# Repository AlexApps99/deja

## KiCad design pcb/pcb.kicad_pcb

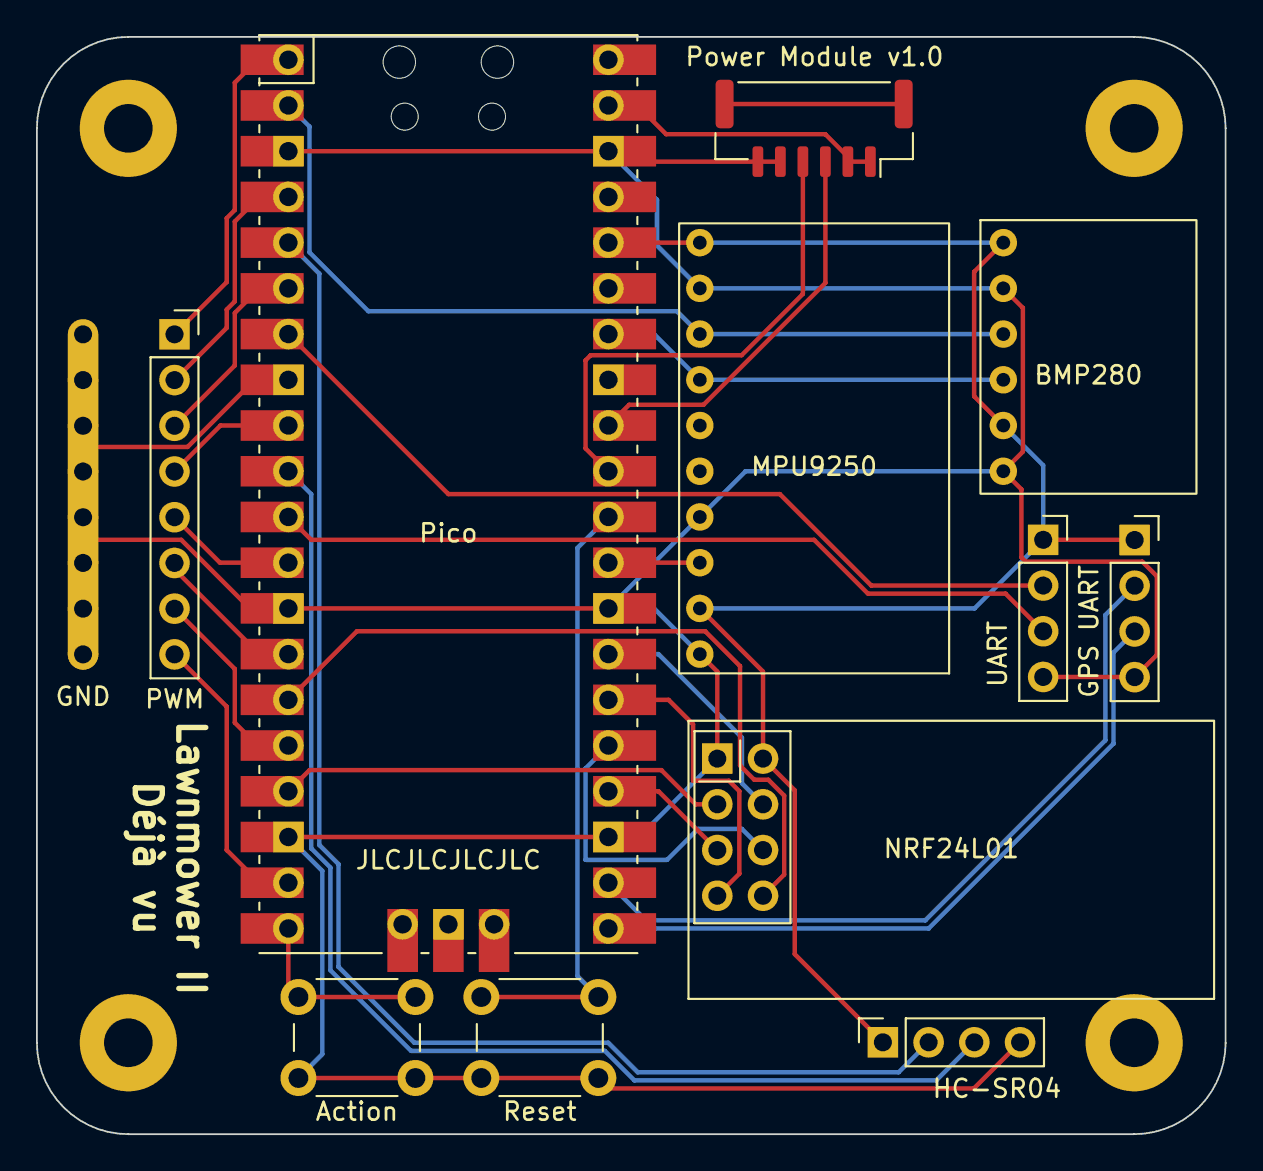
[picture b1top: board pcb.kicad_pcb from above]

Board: 2 copper layers, 66.0 x 61.0 mm, 12 parts (0 on the bottom side), 30 nets.

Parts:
J1: GND; PowerRail8
J2: HC-SR04; PinSocket_1x04_P2.54mm_Vertical
J3: PWM; PinSocket_1x08_P2.54mm_Vertical
J4: GPS UART; PinSocket_1x04_P2.54mm_Vertical
J5: Power Module v1.0; JST_GH_SM06B-GHS-TB_1x06-1MP_P1.25mm_Horizontal
J6: UART; PinSocket_1x04_P2.54mm_Vertical
SW1: Reset; SW_PUSH_6mm_H8mm
SW2: Action; SW_PUSH_6mm_H8mm
U1: Pico; RPi_Pico_SMD_TH
U2: NRF24L01; nRF24L01_Breakout
U3: MPU9250
U4: BMP280

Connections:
+3.3V: J2.1, J4.1, J6.1, U1.36 (3V3), U2.2 (VCC), U3.1 (VCC), U3.9 (NCS), U4.1 (VIN), U4.5 (CSB)
GND: J1.1, J2.4, J4.4, J5.5 (GND), J5.6 (GND), J6.4, SW1.2, SW2.2, U1.3 (GND), U1.8 (GND), U1.13 (GND), U1.18 (GND), U1.23 (GND), U1.28 (GND), U1.38 (GND), U2.1 (GND), U3.2 (GND), U3.7 (AD0), U3.10 (FSYNC), U4.2 (GND), U4.6 (SDD)
unnamed: J2.2, U1.5 (GPIO3)
unnamed: J2.3, U1.10 (GPIO7)
unnamed: J3.1, U1.1 (GPIO0)
unnamed: J3.2, U1.4 (GPIO2)
unnamed: J3.3, U1.6 (GPIO4)
unnamed: J3.4, U1.9 (GPIO6)
unnamed: J3.5, U1.12 (GPIO9)
unnamed: J3.6, U1.14 (GPIO10)
unnamed: J3.7, U1.16 (GPIO12)
unnamed: J3.8, U1.19 (GPIO14)
unnamed: J4.2, U1.22 (GPIO17)
unnamed: J4.3, U1.21 (GPIO16)
unnamed: J5.1 (5V), J5.2 (5V), U1.39 (VSYS)
unnamed: J5.3 (Current), U1.32 (GPIO27_ADC1)
unnamed: J5.4 (Voltage), U1.31 (GPIO26_ADC0)
unnamed: J6.2, U1.7 (GPIO5)
unnamed: J6.3, U1.11 (GPIO8)
unnamed: SW1.1, U1.30 (RUN)
unnamed: SW2.1, U1.20 (GPIO15)
unnamed: U1.15 (GPIO11), U2.8 (IRQ)
unnamed: U1.17 (GPIO13), U2.3 (CE)
unnamed: U1.24 (GPIO18), U2.5 (SCK)
unnamed: U1.25 (GPIO19), U2.6 (MOSI)
unnamed: U1.26 (GPIO20), U2.7 (MISO)
unnamed: U1.27 (GPIO21), U2.4 (~CSN)
unnamed: U1.29 (GPIO22), U3.8 (INT)
SCL: U1.2 (GPIO1), U3.3 (SCL), U4.3 (SCL)
SDA: U1.34 (GPIO28_ADC2), U3.4 (SDA), U4.4 (SDA)

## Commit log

2022-07-27 Skeleton set up! PCB done! Let's go!
2022-07-31 More sweeping changes, soon IO will be done?
2022-08-02 Refactored organization
2022-08-26 We're going places! A lot of things work now!
2022-11-02 Unstaged stuff
